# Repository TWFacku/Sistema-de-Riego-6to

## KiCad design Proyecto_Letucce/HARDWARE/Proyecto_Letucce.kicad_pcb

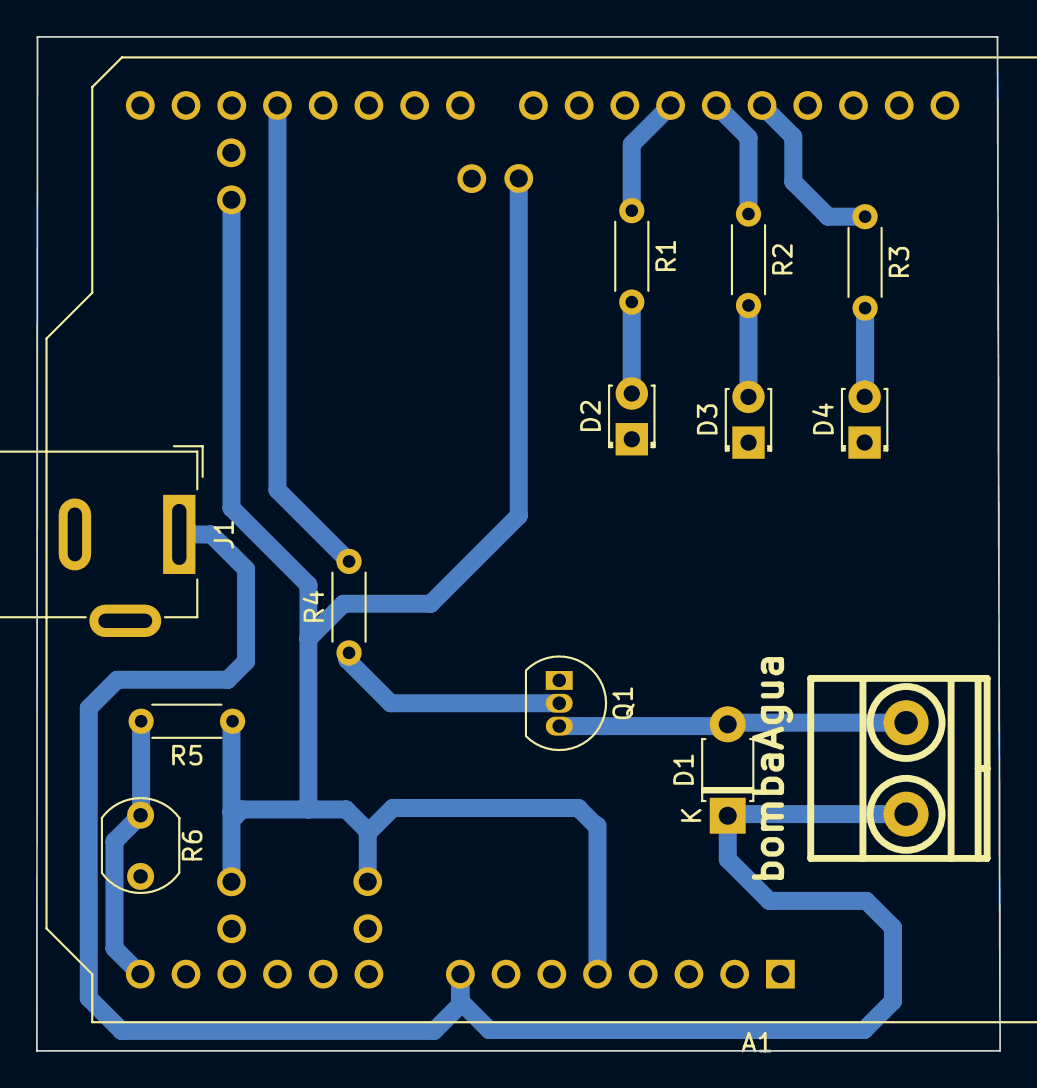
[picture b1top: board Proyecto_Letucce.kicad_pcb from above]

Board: 2 copper layers, 53.5 x 56.3 mm, 14 parts (0 on the bottom side), 13 nets.

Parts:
A1: Arduino_UNO_R3
D1: D; D_T-1_P5.08mm_Horizontal
D2, D3, D4: LED; LED_D1.8mm_W3.3mm_H2.4mm
J1: Jack-DC; BarrelJack_Wuerth_6941xx301002
J9: bombaAgua; BORNERA2
Q1: PN2222A; TO-92_Inline
R1, R2, R3, R4: 220; R_Axial_DIN0204_L3.6mm_D1.6mm_P5.08mm_Horizontal
R5: 1k; R_Axial_DIN0204_L3.6mm_D1.6mm_P5.08mm_Horizontal
R6: LDR07; R_LDR_5.1x4.3mm_P3.4mm_Vertical

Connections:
/D3: A1.18 (D3), R4.2
/D11: A1.26 (D11), R1.1
/D12: A1.27 (D12), R2.1
/D13: A1.28 (D13), R3.1
/LDR: A1.14 (SCL/A5), R5.2, R6.1
/bateria: A1.8 (VIN), D1.1 (K), J1.1, J9.1
GND: A1.6 (GND), A1.7 (GND), A1.29 (GND), D2.1 (K), D3.1 (K), D4.1 (K), Q1.1 (E), R6.2
unnamed: D1.2 (A), J9.2, Q1.3 (C)
unnamed: D2.2 (A), R1.2
unnamed: D3.2 (A), R2.2
unnamed: D4.2 (A), R3.2
unnamed: Q1.2 (B), R4.1
VCC: A1.5 (+5V), R5.1

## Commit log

2022-11-24 Proyecto_Letucce HARDWARE
    contine elementos de la placa tanto como SCH como PCB.
2022-11-24 PCB.
    PCB placa final del proyecto.
2022-11-24 pre-informe
    informe realizado para tener una idea del proyecto a realizar.
